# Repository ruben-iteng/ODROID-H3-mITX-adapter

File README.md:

<div align="center" markdown="1">

  <h1>ODROID H3(+) mITX adapter</h1>

  A feature rich mITX adapter for the ODROD H3(+) <br>
  Designed for the [NaSFW project](https://github.com/IoannisP-ITENG/NaSFW)

</div>

## Features

- 1x12 header exposing ODROID GPIO
  - I2C1
  - I2C2
  - HDMI_CEC
  - UART_RTS
  - UART_CTS
- 1x10 header exposing ESP32 GPIO
  - GPIO4
  - GPI36
  - GPIO14
  - GPIO14 5V OUT
  - GPIO12
- 1x6 header exposing ESP32 programming
  - Pin conmpatible with FT232 boards
  - 3V3
  - RX
  - TX
- Front IO
  - 2xUSB2.0 header
  - Front IO header
    - Power LED connected to +5V_RUN
    - HDD connected to ESP32 GPIO4
    - PWR button connected to ODROID
    - RESET button connected to ESP32 GPI39
- On board USB2.0 A connector to ODROID (USB1)
- All USB
  - D+/D- ESD protection
  - VBUS protection
  - VBUS switchable by eitgher
    - ESP32
    - +5V_RUN
- ESP32 with Ethernet
  - Remote UART terminal (BIOS access)
  - 3x USB power control
  - Reset button input
  - PWR_ON button controll of ODROID via optocoupler
  - Always-on, powered by +5V_STBY or USB Type-C PD input

## Manufacturing

Designed for ordering and assembly by JLCPCB

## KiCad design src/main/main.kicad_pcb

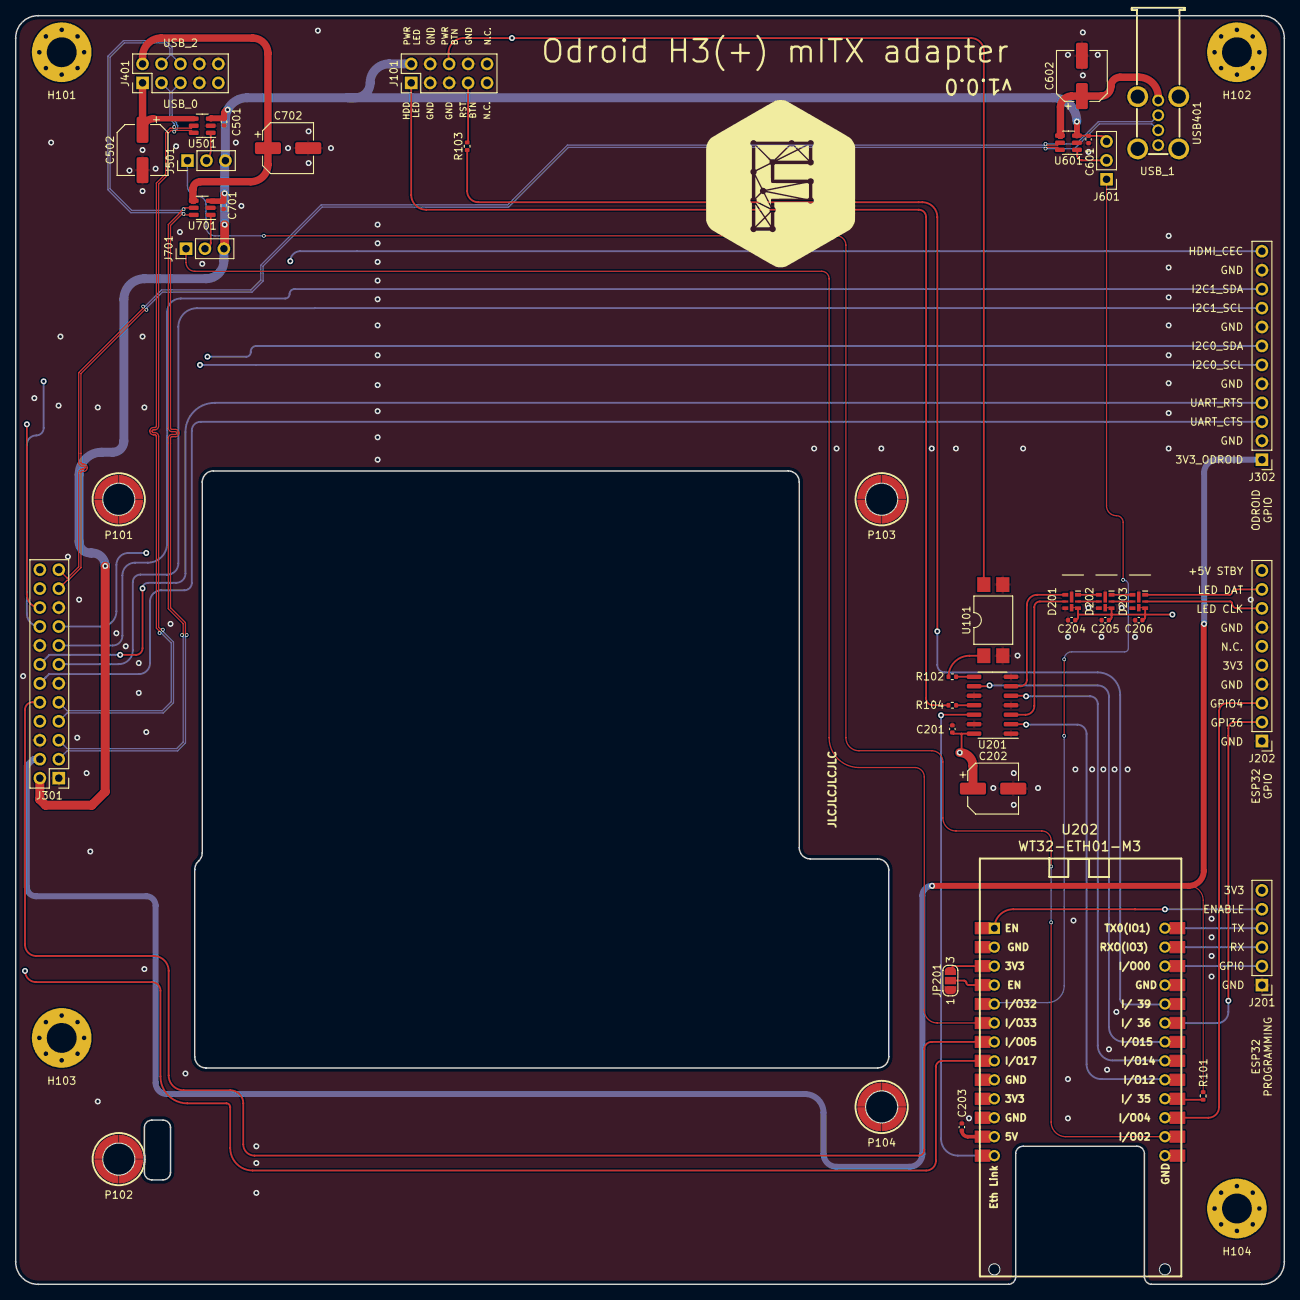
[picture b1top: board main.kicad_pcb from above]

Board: 4 copper layers, 170.0 x 170.0 mm, 44 parts (0 on the bottom side), 56 nets.

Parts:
C201, C203, C204, C205, C206, C501, C601, C701: 100nF; C_0402_1005Metric
C202, C502, C602, C702: 150uF 10V ±20%; CP_Elec_6.3x7.7
D201, D202, D203: APA102-2020; LED-APA102-2020
H101, H102, H103, H104: MountingHole_Pad; MountingHole_4mm_Pad_Via
J101, J401: Conn_02x05_Odd_Even; PinHeader_2x05_P2.54mm_Vertical
J201: Conn_01x06; PinHeader_1x06_P2.54mm_Vertical
J202: Conn_01x10; PinHeader_1x10_P2.54mm_Vertical
J301: Conn_02x12_Odd_Even; PinHeader_2x12_P2.54mm_Vertical
J302: Conn_01x12; PinHeader_1x12_P2.54mm_Vertical
J501, J601, J701: Conn_01x03; PinHeader_1x03_P2.54mm_Vertical
JP201: Jumper_3_Open; SolderJumper-3_P1.3mm_Open_RoundedPad1.0x1.5mm_NumberLabels
P101, P102, P103, P104: SMTSO3035CTJ; SMD_BD5.6-D4.1
R101, R103: 1K; R_0402_1005Metric
R102, R104: 100R; R_0402_1005Metric
U101: LTV-817S; SMDIP-4_W9.53mm
U201: CD74HCT125M96; SOIC-14_3.9x8.7mm_P1.27mm
U202: WT32-ETH01-M3; WT32-ETH01
U501, U601, U701: TPD3S014; SOT-23-6
USB401: USB-226-BRY

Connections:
/+5V_RUN: C501.1, C601.1, C701.1, J101.2, J301.2, J501.3, J601.3, J701.3, U501.3 (IN), U601.3 (IN), U701.3 (IN)
/ETH_LINK: R104.1, U201.11
/HDD_LED_P: J101.1, R104.2
/Odroid H3+/12C0_SDA: J301.20, J302.7
/Odroid H3+/12C1_SDA: J301.15, J302.10
/Odroid H3+/+3V3_RUN: J301.4, J302.1, R101.2
/Odroid H3+/HDMI_CEC: J301.22, J302.12
/Odroid H3+/I2C0_SCL: J301.18, J302.6
/Odroid H3+/I2C1_SCL: J301.13, J302.9
/Odroid H3+/UART0_CTS: J301.12, J302.3
/Odroid H3+/UART0_RTS: J301.14, J302.4
/Odroid H3+/UART0_RX: J301.8, U202.8 (TxD2_(I/O17))
/Odroid H3+/UART0_TX: J301.10, U202.7 (RxD2_(I/O5))
/PWR_BTN: J101.6, J301.17, U101.4
/PWR_ON: R102.1, U201.8
/RST_BTN: J101.7, R103.2
/USB/USB0_DN: J301.9, J401.3, U501.5 (D1)
/USB/USB0_DP: J301.7, J401.5, U501.6 (D2)
/USB/USB0_EN: J501.1, U202.15 (I/O2)
/USB/USB1_DN: J301.23, U601.5 (D1), USB401.2 (D-)
/USB/USB1_DP: J301.21, U601.6 (D2), USB401.3 (D+)
/USB/USB1_EN: J601.1, U202.5 (CFG_(I/O32))
/USB/USB2_DN: J301.5, J401.4, U701.5 (D1)
/USB/USB2_DP: J301.3, J401.6, U701.6 (D2)
/USB/USB2_EN: J701.1, U202.6 (485_EN(I/O33))
/USB/VBUS_0: C502.1, J401.1, U501.4 (OUT)
/USB/VBUS_1: C602.1, U601.4 (OUT), USB401.1 (VBUS)
/USB/VBUS_2: C702.1, J401.2, U701.4 (OUT)
/WT32-ETH01/+3V3_ESP: J201.6, J202.5, JP201.3 (B), U202.3 (3V3), U202.10 (3V3)
/WT32-ETH01/+5V_STBY: C201.1, C202.1, C203.1, C204.1, C205.1, C206.1, D201.1 (VDD), D202.1 (VDD), D203.1 (VDD), J202.10, J301.24, U201.14 (VCC), U202.12 (5V0)
/WT32-ETH01/ENABLE: J201.5, U202.1 (EN)
/WT32-ETH01/ETH_LLINK: U201.12, U202.13 (Eth_Link)
/WT32-ETH01/GPI0: J201.2, U202.24 (I/O0)
/WT32-ETH01/GPI36: J202.2, U202.21 (I/O36)
/WT32-ETH01/GPI39: R103.1, U202.22 (I/O39)
/WT32-ETH01/GPIO04: J202.3, U202.16 (I/O4)
/WT32-ETH01/LED_CLK_HV: D201.5 (CKI), U201.3
/WT32-ETH01/LED_CLK_LV: U201.2, U202.18 (I/O12)
/WT32-ETH01/LED_CLOCK_OUT: D203.2 (CKO), J202.8
/WT32-ETH01/LED_DATA_OUT: D203.3 (SDO), J202.9
/WT32-ETH01/LED_DAT_HV: D201.4 (SDI), U201.6
/WT32-ETH01/LED_DAT_LV: U201.5, U202.19 (I/O14)
/WT32-ETH01/PWR_ON_LV: U201.9, U202.20 (I/O15)
/WT32-ETH01/PWR_SENSE: R101.1, U202.17 (I/O35)
/WT32-ETH01/UART_PROG_RX: J201.3, U202.25 (RxD0_(I/O3))
/WT32-ETH01/UART_PROG_TX: J201.4, U202.26 (TxD0_(I/O1))
GND: C201.2, C202.2, C203.2, C204.2, C205.2, C206.2, C501.2, C502.2, C601.2, C602.2, C701.2, C702.2, D201.6 (GND), D202.6 (GND), D203.6 (GND), J101.3, J101.4, J101.5, J101.8, J201.1, J202.1, J202.4, J202.7, J301.1, J301.6, J301.11, J301.16, J301.19, J302.2, J302.5, J302.8, J302.11, J401.7, J401.8, J401.10, JP201.1 (A), U101.2, U101.3, U201.1, U201.4, U201.7 (GND), U201.10, U201.13, U202.2 (Gnd), U202.9 (Gnd), U202.11 (Gnd), U202.14 (Gnd), U202.23 (Gnd), U501.2 (GND), U601.2 (GND), U701.2 (GND), USB401.4 (GND), USB401.5 (Shield)
unnamed: D201.2 (CKO), D202.5 (CKI)
unnamed: D201.3 (SDO), D202.4 (SDI)
unnamed: D202.2 (CKO), D203.5 (CKI)
unnamed: D202.3 (SDO), D203.4 (SDI)
unnamed: J501.2, U501.1 (EN)
unnamed: J601.2, U601.1 (EN)
unnamed: J701.2, U701.1 (EN)
unnamed: JP201.2 (C), U202.4 (EN1)
unnamed: R102.2, U101.1

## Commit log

2023-05-07 Add git related files
2023-05-07 rev1.0.0
2023-05-07 Fix wrong path
2023-05-07 Fix wrong header pinout
2023-05-07 Update 3D image
2023-05-07 Fix KiCad exclude issue
2023-05-07 rev1.0.0 (#1)
    A feature rich mITX adapter for the ODROD H3(+)
2023-06-24 rev1.1.0
    - J201 programming header
    - Add reset button
    - Add enable button
    - Make pinout compatible with USB-UART boards
    - Move GPI0 and ENABLE to testpoints
    - Add power rail LED status indicators
2023-08-13 Additions and fixes:
    Add:
    - Add power rail LED status indicators
    - Buffered LED on ETH_LINK
    - GPIO14 and GPIO12 on header
    - GPIO14 5V buffered output on header
    - Testpoints for GPIO0 and ESP32_ENABLE pin
2023-08-13 Fix U201 missing from BOM
2023-08-13 Rev1.1.0: (#7)
    Add:
    - Power rail LED status indicators
    - Buffered LED on ETH_LINK
    - GPIO14 and GPIO12 on header
    - GPIO14 5V buffered output on header
    - Testpoints for GPIO0 and ESP32_ENABLE pin
